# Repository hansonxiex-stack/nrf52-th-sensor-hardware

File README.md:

# nRF52 温湿度传感器 · 四层 PCB 硬件工程

基于 **nRF52810** 的低功耗 BLE 温湿度传感器：CR2032 纽扣电池直接供电，SHT40 采集温湿度，HT16C21A 驱动段码 LCD 常显，板载 2.4 GHz PCB 天线对外广播。

工程从需求分析、原理图、四层 PCB 布局布线，做到电源仿真、信号／电源完整性分析、热设计、DFM 整改与生产文件交付，完整走完一遍从需求到制造文件的硬件设计流程。

> **本工程只做设计、仿真与可制造性分析，未提交订单、未产生实际支付。**
> 文档中出现的板厂报价截图均为下单页快照，用于比较工艺选项的成本，不代表已下单。

---

## 关键指标

| 项目 | 参数 |
|---|---|
| 板框尺寸 | 48.25 × 40.05 mm |
| 层数 / 叠层 | 4 层，S-G-P-S（信号-地-电源-信号） |
| 板厚 | 1.6062 mm（成品 1.6 mm 级） |
| 主控 | nRF52810 QFN48，0.4 mm 间距 |
| 传感器 | SHT40（I²C，±1.8 %RH / ±0.2 °C） |
| 显示 | HT16C21A + 20×4 段码 LCD |
| 供电 | CR2032 3.0 V 直供，不经 LDO |
| 无线 | 2.4 GHz 板载 PCB 天线，50 Ω 馈线 W ≈ 0.36 mm |
| I²C | 100 kHz，10 kΩ 上拉 |
| 低电量阈值 | 2.8 V 告警；系统工作下限 2.4 V |
| BOM | 23 行 / 31 个位号，标准带屏版约 28.36 元 |
| DRC | 0 error、0 未连接 |

---

## 系统组成

```
        ┌──────────┐   I²C    ┌────────────┐
 CR2032 ─┤ SHT40    ├──────────┤ nRF52810   ├── SWD ── J1（U4 ESD 保护）
  3.0 V  └──────────┘          │            │
                              │            ├── 2.4 GHz PCB 天线
                     I²C      │            │
        ┌────────────┐        │            │
        │ HT16C21A   ├────────┴────────────┘
        │     ↓      │
        │  段码 LCD  │
        └────────────┘
```

三条路径：**数据**（SHT40 → nRF52810 → 段码 LCD、天线）、**供电**（CR2032 直供三个模块）、**调试**（SWD 三线，入口处 U4 做 ESD 保护）。

---

## 目录结构

```
.
├── hardware/          KiCad 10 工程、自定义符号与封装、ERC/DRC 报告
├── simulation/        LTspice 电源仿真电路与运行日志
├── manufacturing/     生产文件包（Gerber、钻孔、BOM、CPL、制板说明）
├── docs/              8 周实验报告与各专项设计说明（Markdown）
├── presentation/      项目演示 PPT（含逐页讲解录音）、PDF 与讲解稿
└── images/            3D 图、系统框图、流程框图、关键布局图
```

各目录下的文件命名即对应周次与主题，`docs/wk1` … `docs/wk8` 按八周实验顺序排列。

---

## 设计要点

**叠层与阻抗** — 采用 S-G-P-S 四层结构。顶层射频馈线以下方地平面（In1.GND）为参考，按介质厚度 0.2104 mm、Er ≈ 4.4 反算 50 Ω 对应线宽约 0.36 mm；QFN 引脚出口受焊盘间距限制，局部采用约 0.7 mm 的短颈缩，其余馈线保持顶层连续、避免过孔。

**布局分区** — 射频链路单独占一角并保持参考地完整；SHT40 布置在板边、与主控中心距离约 25.5 mm，器件下方设置四层禁铜区，降低板内热耦合；晶振与负载电容贴近对应引脚，去耦电容结合电源引脚布置。

**电源完整性** — CR2032 直供省掉 LDO 压差损失。LTspice 中以电压源＋电池内阻＋等效脉冲负载＋去耦电容建模，扫描 10 / 30 / 50 Ω 三档内阻，最低电压约 2.499 V；PCB 自身压降小于 0.5 mV，电压波动主要来自电池内阻。

**接口与防护** — I²C 综合驱动供电条件采用 100 kHz，按约 30 pF 总线电容估算上升时间约 254 ns；SHT40 与 HT16C21A 地址不冲突，共用一路总线。SWD 入口 U4 在保护性能与低功耗之间取舍，重点控制漏电流。

**可制造性** — DRC 收口到 0 error、0 未连接；DFM 报出的 96 条危险按封装模型差异、贴装方向与盘中孔工艺逐条分类核对，U1 散热盘盘中孔在制板说明中明确采用 POFV 工艺（IPC-4761 Type VII）。

---

## 工具

| 环节 | 工具 |
|---|---|
| 原理图 / PCB | KiCad 10.0 |
| 电源仿真 | LTspice |
| 阻抗计算 | 板厂阻抗计算器 + 手工反算交叉验证 |
| 可制造性 | 板厂 DRC / DFM 分析 + 人工逐条核对 |

---

## 文档索引

| 文档 | 内容 |
|---|---|
| [`docs/项目理解与个人8周计划`](docs/项目理解与个人8周计划.md) | 项目理解与八周安排 |
| [`docs/变更记录表_智能温湿度传感器`](docs/变更记录表_智能温湿度传感器.md) | 全流程变更与决策记录 |
| [`docs/wk1`](docs/wk1) | 产品需求分析、引脚分配 |
| [`docs/wk2`](docs/wk2) | 器件选型、符号库、LTspice 入门 |
| [`docs/wk3`](docs/wk3) | 四层叠层设计与阻抗计算 |
| [`docs/wk4`](docs/wk4) | 布局布线 |
| [`docs/wk5`](docs/wk5) | DRC、ESD 与滤波、电源模块布线 |
| [`docs/wk6`](docs/wk6) | 信号完整性、电源完整性、热设计、DFT |
| [`docs/wk7`](docs/wk7) | DFM、BOM 与工艺、生产文件包清单、贴装方向说明 |
| [`docs/wk8`](docs/wk8) | 项目总结报告、交付确认说明 |
| [`presentation/项目演示PPT_讲解稿`](presentation/项目演示PPT_讲解稿.md) | 22 页演示的逐页讲稿 |

---

## 说明

- 本工程为个人学习过程中的完整硬件设计练习，器件选型、参数取值与工艺决策均在文档中给出依据。
- 板厂报价与工艺选项以截图形式记录，仅用于说明取舍过程。
- 演示录像体积较大，未随仓库提供。

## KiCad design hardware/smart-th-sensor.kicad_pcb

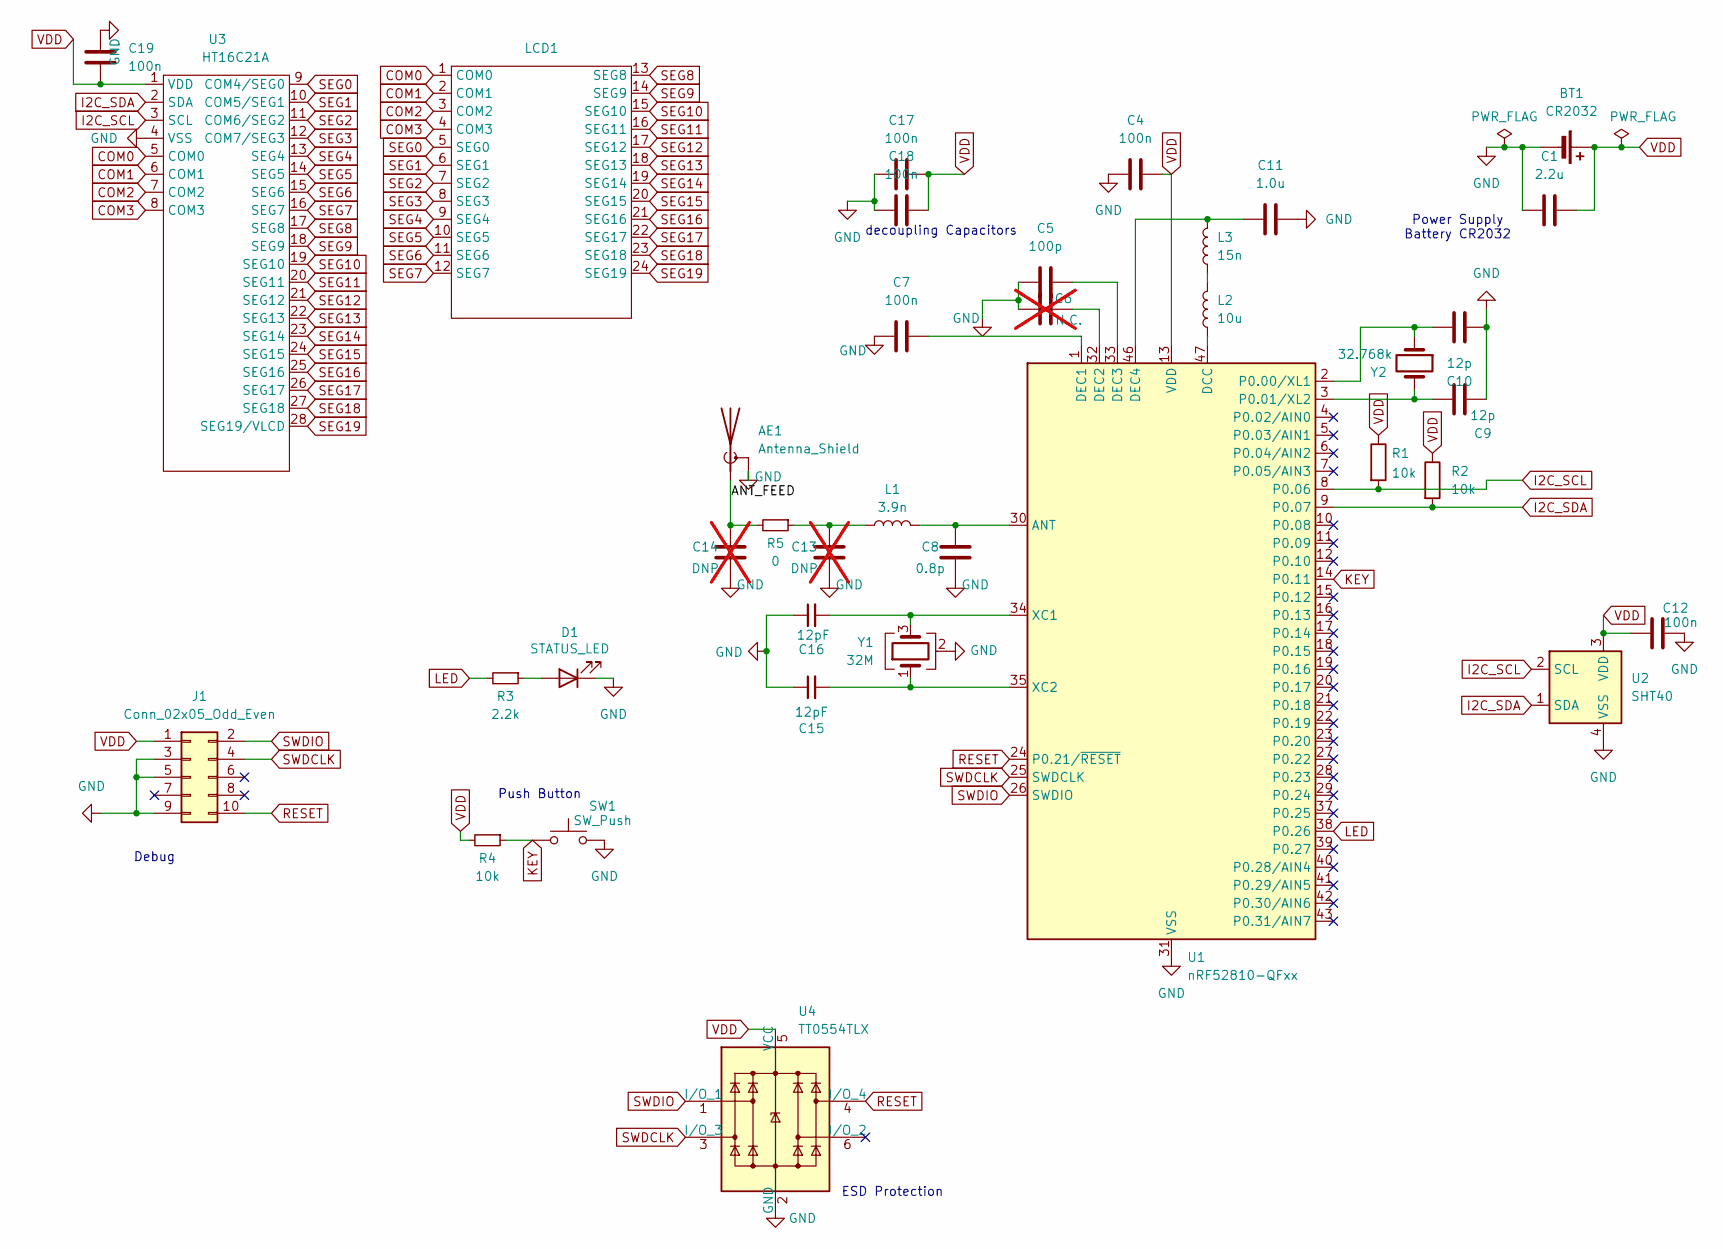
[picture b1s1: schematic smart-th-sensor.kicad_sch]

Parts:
AE1: Antenna_Shield; Texas_SWRA117D_2.4GHz_Left
BT1: CR2032; BatteryHolder_MYOUNG_BS-07-A1BJ001_CR2032
C1: 2.2u; C_0805_2012Metric
C4, C7, C17, C18, C19: 100n; C_0402_1005Metric
C5: 100p; C_0402_1005Metric
C6: N.C.; C_0402_1005Metric; not fitted
C8: 0.8p; C_0402_1005Metric
C9, C10: 12p; C_0402_1005Metric
C11: 1.0u; C_0603_1608Metric
C12: 100n; C_0805_2012Metric
C13, C14: DNP; C_0402_1005Metric; not fitted
C15, C16: 12pF; C_0805_2012Metric
D1: STATUS_LED; LED_0805_2012Metric_Pad1.15x1.40mm_HandSolder
J1: Conn_02x05_Odd_Even; PinHeader_2x05_P1.27mm_Vertical_SMD
L1: 3.9n; L_0402_1005Metric
L2: 10u; L_0805_2012Metric
L3: 15n; L_0402_1005Metric
LCD1: LCD_Segment_20x4
R1, R2, R4: 10k; R_0805_2012Metric
R3: 2.2k; R_0805_2012Metric
R5: 0; R_0402_1005Metric
SW1: SW_Push; SW_SPST_PTS810
U1: nRF52810-QFxx; QFN-48-1EP_6x6mm_P0.4mm_EP4.6x4.6mm
U2: SHT40; Sensirion_DFN-4_1.5x1.5mm_P0.8mm_SHT4x_NoCentralPad
U3: HT16C21A; SSOP-28_3.9x9.9mm_P0.635mm
U4: TT0554TLX; SOT-23-6
Y1: 32M; Crystal_SMD_2016-4Pin_2.0x1.6mm
Y2: 32.768k; Crystal_SMD_3215-2Pin_3.2x1.5mm

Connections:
/ANT_FEED: AE1.1 (A), C14.2, R5.2
COM0: LCD1.1 (COM0), U3.5 (COM0)
COM1: LCD1.2 (COM1), U3.6 (COM1)
COM2: LCD1.3 (COM2), U3.7 (COM2)
COM3: LCD1.4 (COM3), U3.8 (COM3)
GND: AE1.2 (Shield), BT1.2 (-), C1.1, C4.1, C5.1, C6.1, C7.1, C8.1, C9.1, C10.1, C11.2, C12.2, C13.1, C14.1, C15.1, C16.1, C17.1, C18.1, C19.1, D1.1 (K), J1.3, J1.5, J1.9, SW1.2, U1.31 (VSS), U1.45 (VSS), U1.49 (VSS), U2.4 (VSS), U3.4 (VSS), U4.2 (GND), Y1.2 (G), Y1.4 (G)
I2C_SCL: R1.2, U1.8 (P0.06), U2.2 (SCL), U3.3 (SCL)
I2C_SDA: R2.2, U1.9 (P0.07), U2.1 (SDA), U3.2 (SDA)
KEY: R4.1, SW1.1, U1.14 (P0.11)
LED: R3.2, U1.38 (P0.26)
unnamed: C13.2, L1.1, R5.1
unnamed: D1.2 (A), R3.1
unnamed: L2.2, L3.1
unnamed: C8.2, L1.2, U1.30 (ANT)
unnamed: L2.1, U1.47 (DCC)
unnamed: C7.2, U1.1 (DEC1)
unnamed: C6.2, U1.32 (DEC2)
unnamed: C5.2, U1.33 (DEC3)
unnamed: C11.1, L3.2, U1.46 (DEC4)
unnamed: C10.2, U1.2 (P0.00/XL1), Y2.1
unnamed: C9.2, U1.3 (P0.01/XL2), Y2.2
unnamed: C16.2, U1.34 (XC1), Y1.3
unnamed: C15.2, U1.35 (XC2), Y1.1
RESET: J1.10, U1.24 (P0.21/~RESET), U4.4 (I/O_4)
SEG0: LCD1.5 (SEG0), U3.9 (COM4/SEG0)
SEG1: LCD1.6 (SEG1), U3.10 (COM5/SEG1)
SEG2: LCD1.7 (SEG2), U3.11 (COM6/SEG2)
SEG3: LCD1.8 (SEG3), U3.12 (COM7/SEG3)
SEG4: LCD1.9 (SEG4), U3.13 (SEG4)
SEG5: LCD1.10 (SEG5), U3.14 (SEG5)
SEG6: LCD1.11 (SEG6), U3.15 (SEG6)
SEG7: LCD1.12 (SEG7), U3.16 (SEG7)
SEG8: LCD1.13 (SEG8), U3.17 (SEG8)
SEG9: LCD1.14 (SEG9), U3.18 (SEG9)
SEG10: LCD1.15 (SEG10), U3.19 (SEG10)
SEG11: LCD1.16 (SEG11), U3.20 (SEG11)
SEG12: LCD1.17 (SEG12), U3.21 (SEG12)
SEG13: LCD1.18 (SEG13), U3.22 (SEG13)
SEG14: LCD1.19 (SEG14), U3.23 (SEG14)
SEG15: LCD1.20 (SEG15), U3.24 (SEG15)
SEG16: LCD1.21 (SEG16), U3.25 (SEG16)
SEG17: LCD1.22 (SEG17), U3.26 (SEG17)
SEG18: LCD1.23 (SEG18), U3.27 (SEG18)
SEG19: LCD1.24 (SEG19), U3.28 (SEG19/VLCD)
SWDCLK: J1.4, U1.25 (SWDCLK), U4.3 (I/O_3)
SWDIO: J1.2, U1.26 (SWDIO), U4.1 (I/O_1)
VDD: BT1.1 (+), C1.2, C4.2, C12.1, C17.2, C18.2, C19.2, J1.1, R1.1, R2.1, R4.2, U1.13 (VDD), U1.36 (VDD), U1.48 (VDD), U2.3 (VDD), U3.1 (VDD), U4.5 (VCC)

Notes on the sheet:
decoupling Capacitors
ESD Protection
Push Button
Debug
Power Supply Battery CR2032

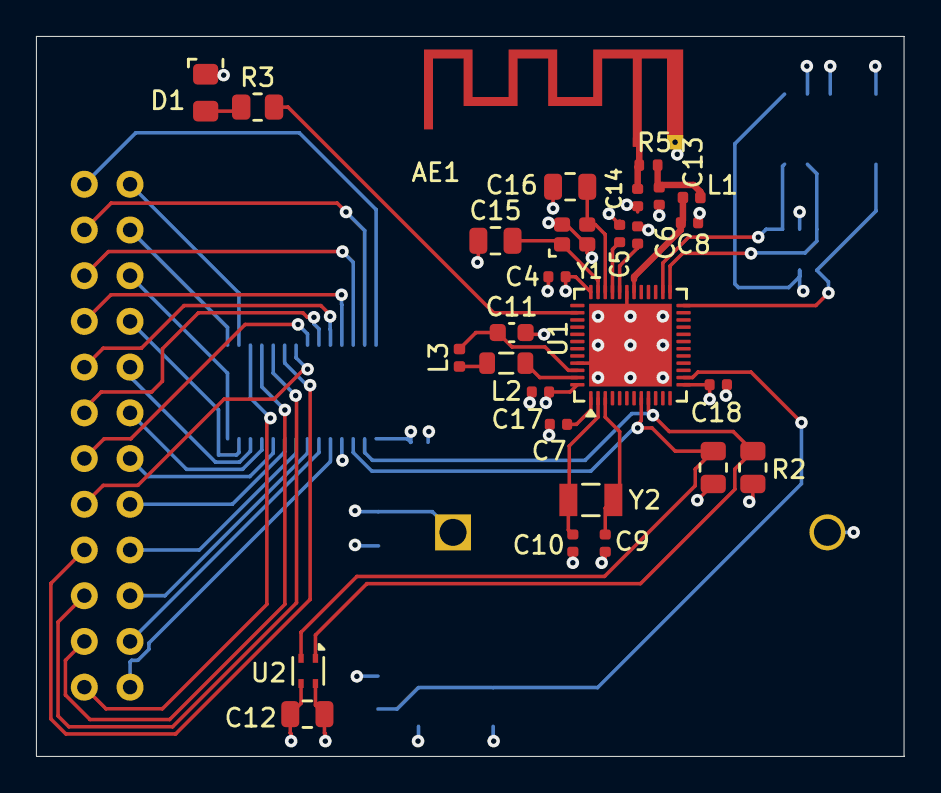
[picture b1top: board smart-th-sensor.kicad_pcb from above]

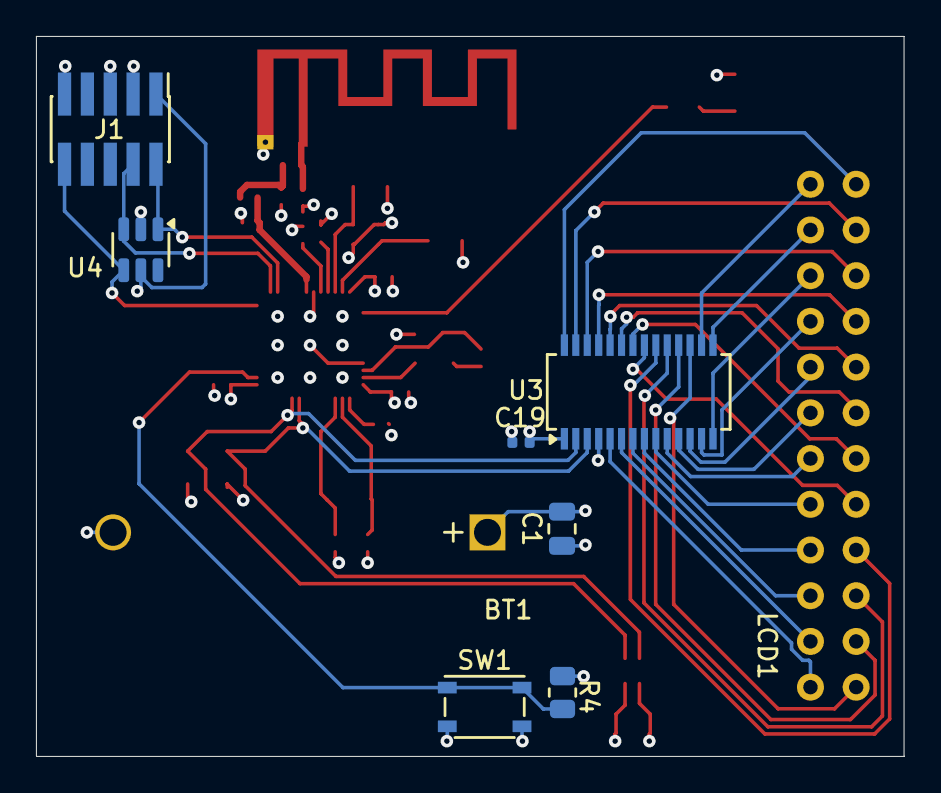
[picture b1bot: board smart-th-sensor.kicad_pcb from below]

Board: 4 copper layers, 48.2 x 40.0 mm, 37 parts (9 on the bottom side), 47 nets.

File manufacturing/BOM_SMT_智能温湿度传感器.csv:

Comment,Designator,Footprint,LCSC Part #,Quantity
2.2u,C1,C_0805_2012Metric,C77081,1
100n,"C4,C7,C17,C18,C19",C_0402_1005Metric,C1525,5
100p,C5,C_0402_1005Metric,C1546,1
0.8p,C8,C_0402_1005Metric,C285068,1
12p,"C9,C10",C_0402_1005Metric,C1547,2
1.0u,C11,C_0603_1608Metric,C15849,1
100n,C12,C_0805_2012Metric,C49678,1
12pF,"C15,C16",C_0805_2012Metric,C107108,2
STATUS_LED,D1,LED_0805_2012Metric_Pad1.15x1.40mm_HandSolder,C2297,1
Conn_02x05_Odd_Even,J1,PinHeader_2x05_P1.27mm_Vertical_SMD,C51897894,1
3.9n,L1,L_0402_1005Metric,C14033,1
10u,L2,L_0805_2012Metric,C162582,1
15n,L3,L_0402_1005Metric,C27143,1
10k,"R1,R2,R4",R_0805_2012Metric,C17414,3
2.2k,R3,R_0805_2012Metric,C17520,1
0,R5,R_0402_1005Metric,C17168,1
SW_Push,SW1,SW_SPST_PTS810,C221895,1
nRF52810-QFxx,U1,QFN-48-1EP_6x6mm_P0.4mm_EP4.6x4.6mm,C141828,1
SHT40,U2,Sensirion_DFN-4_1.5x1.5mm_P0.8mm_SHT4x_NoCentralPad,C2909890,1
HT16C21A,U3,SSOP-28_3.9x9.9mm_P0.635mm,C5444716,1
TT0554TLX,U4,SOT-23-6,C5156695,1
32MHz,Y1,Crystal_SMD_2016-4Pin_2.0x1.6mm,C3013600,1
32.768k,Y2,Crystal_SMD_3215-2Pin_3.2x1.5mm,C5120558,1
